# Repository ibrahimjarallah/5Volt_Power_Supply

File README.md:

# 5V Regulated Power Supply — L7805 Based PCB

> A classic linear regulated 5V power supply built around the L7805 voltage regulator.  
> Full-wave bridge rectifier input, multi-stage filtering, and power LED indicator.  
> Designed and laid out in **KiCad 9.0** — schematic + 2-layer PCB with full fabrication outputs.

---

## 📸 3D Views

| Front | Back |
|:---:|:---:|
|  |  |

## 🖼️ PCB Layout (2D)

| Front | Back |
|:---:|:---:|
|  |  |

## 🟤 PCB Layout — Copper Fill (2D)

| Front | Back |
|:---:|:---:|
|  |  |

## 📐 Schematic

---

## ⚡ Specifications

| Parameter             | Value                              |
|-----------------------|------------------------------------|
| Input Voltage (AC)    | 9V AC (transformer secondary)      |
| Rectified DC (unregulated) | ~12.7V DC                   |
| Output Voltage        | 5V DC regulated                    |
| Max Output Current    | 500mA continuous (no heatsink)     |
| Regulator             | L7805 (TO-220)                     |
| Rectifier             | Full-wave bridge — 4× 1N4007       |
| Bulk Capacitance      | 470µF                              |
| PCB Layers            | 2                                  |
| Designed With         | KiCad 9.0.7                        |

---

## 🔧 How It Works

### 1. Rectification
Four **1N4007** diodes arranged in a **full-wave bridge** configuration convert the 9V AC transformer secondary into pulsating DC (~12.7V peak).

### 2. Filtering
A three-stage capacitor filter smooths the rectified DC:
- **C1 (470µF)** — bulk electrolytic, handles low-frequency ripple
- **C2 (0.1µF)** — bypass capacitor, mid-frequency noise suppression
- **C3 (0.01µF)** — high-frequency decoupling at the regulator input

### 3. Regulation
The **L7805** linear regulator drops the unregulated ~12.7V down to a stable **5V DC output**, regardless of load variations up to 500mA.

### 4. Power Indicator
**D5 (LED)** with **R1 (1kΩ)** current-limiting resistor provides a visual power-on indication.  
LED current ≈ (5V − 2V) / 1kΩ ≈ **3mA**.

### 5. Connectors
Two **Phoenix Contact screw terminals (J1, J2)** — 3.5mm pitch — for robust AC input and DC output connections.

---

## 📦 Bill of Materials

| ID | Designator | Description | Quantity | Footprint |
|----|------------|-------------|----------|-----------|
| 1 | U1 | L7805 Voltage Regulator | 1 | TO-220-3 Vertical |
| 2 | D1–D4 | Diode 1N4007 (Bridge Rectifier) | 4 | DO-15 P2.54mm Vertical AnodeUp |
| 3 | D5 | LED 5mm | 1 | LED D5.0mm Horizontal |
| 4 | C1 | Capacitor 470µF electrolytic | 1 | Axial L10.0mm D6.0mm P15.00mm |
| 5 | C2 | Capacitor 0.1µF | 1 | Radial D4.0mm P1.50mm |
| 6 | C3 | Capacitor 0.01µF | 1 | Radial D4.0mm P1.50mm |
| 7 | R1 | Resistor 1kΩ | 1 | Axial DIN0204 L3.6mm P5.08mm |
| 8 | J1, J2 | Screw Terminal 2-pin 3.5mm | 2 | PhoenixContact MC 1.5/2-G-3.5 |

---

## 📁 Repository Structure

```
5Volt_Power_Supply/
├── 5Volt_Power_Supply.kicad_pro     # KiCad project file
├── 5Volt_Power_Supply.kicad_sch     # Schematic
├── 5Volt_Power_Supply.kicad_pcb     # PCB layout
├── BOM/
│   └── 5Volt_Power_Supply.csv       # Bill of materials
├── netlist/
│   └── 5Volt_Power_Supply.net       # Netlist
├── gerbers/                         # Fabrication Gerber files
│   ├── 5Volt_Power_Supply-F_Cu.gbr
│   ├── 5Volt_Power_Supply-B_Cu.gbr
│   ├── 5Volt_Power_Supply-F_Mask.gbr
│   ├── 5Volt_Power_Supply-B_Mask.gbr
│   ├── 5Volt_Power_Supply-F_Silkscreen.gbr
│   ├── 5Volt_Power_Supply-B_Silkscreen.gbr
│   ├── 5Volt_Power_Supply-F_Paste.gbr
│   ├── 5Volt_Power_Supply-B_Paste.gbr
│   ├── 5Volt_Power_Supply-Edge_Cuts.gbr
│   └── 5Volt_Power_Supply-job.gbrjob
├── drills/
│   ├── 5Volt_Power_Supply-PTH.drl   # Plated through-holes
│   └── 5Volt_Power_Supply-NPTH.drl  # Non-plated through-holes
├── 3D_VIEW/
│   ├── front_3d.png
│   └── back_3d.png
├── 2D_VIEW/
│   ├── 2d_view_front.png
│   ├── 2d_view_back.png
│   ├── 2d_view_front_filled.png
│   └── 2d_view_back_filled.png
└── Schematic_view/
    └── schematic_view.png
```

---

## 🖥️ Opening the Project

1. Install [KiCad 9.0+](https://www.kicad.org/download/)
2. Clone this repository:
   ```bash
   git clone https://github.com/ibrahimjarallah/5Volt_Power_Supply.git
   ```
3. Open `5Volt_Power_Supply.kicad_pro` in KiCad

---

## 🏭 Fabrication

All fabrication outputs are ready in the `gerbers/` and `drills/` folders.  
Compatible with standard PCB manufacturers (JLCPCB, PCBWay, OSHPark, etc.).

- Load `5Volt_Power_Supply-job.gbrjob` directly into any Gerber viewer or fab upload portal
- Drill files: `PTH` (plated) and `NPTH` (non-plated) provided separately

---

## ⚠️ Notes

- **No heatsink** — keep output current below 500mA to avoid thermal shutdown of L7805
- **Transformer not included** — requires external 9VAC center-tapped or standard secondary transformer
- **Polarized capacitors** — observe correct polarity for C1 during assembly

---

## 📄 License

This project is licensed under the **MIT License**.  
You are free to use, modify, and distribute it with attribution.

---

## 👤 Author

**Ibrahim Jarallah**  
GitHub: [ibrahimjarallah](https://github.com/ibrahimjarallah) \
LinkedIn: [ibrahimjarallah](https://www.linkedin.com/in/ibrahim-jarallah)

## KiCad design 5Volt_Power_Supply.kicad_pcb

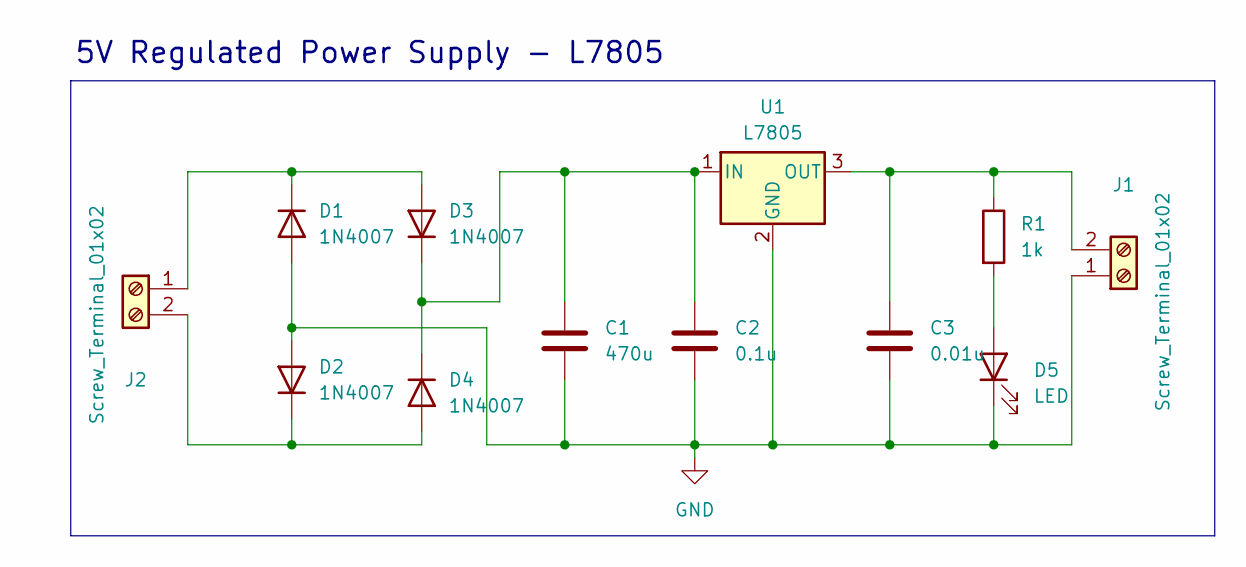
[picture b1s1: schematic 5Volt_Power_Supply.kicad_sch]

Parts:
C1: 470u; CP_Axial_L10.0mm_D6.0mm_P15.00mm_Horizontal
C2: 0.1u; CP_Radial_D4.0mm_P1.50mm
C3: 0.01u; CP_Radial_D4.0mm_P1.50mm
D1, D2, D3, D4: 1N4007; D_DO-15_P2.54mm_Vertical_AnodeUp
D5: LED; LED_D5.0mm_Horizontal_O1.27mm_Z3.0mm
J1, J2: Screw_Terminal_01x02; PhoenixContact_MC_1,5_2-G-3.5_1x02_P3.50mm_Horizontal
R1: 1k; R_Axial_DIN0204_L3.6mm_D1.6mm_P5.08mm_Horizontal
U1: L7805; TO-220-3_Vertical

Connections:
GND: C1.2, C2.2, C3.2, D1.2 (A), D2.2 (A), D5.1 (K), J1.1, U1.2 (GND)
unnamed: D1.1 (K), D3.2 (A), J2.1
unnamed: D2.1 (K), D4.2 (A), J2.2
unnamed: C1.1, C2.1, D3.1 (K), D4.1 (K), U1.1 (IN)
unnamed: D5.2 (A), R1.2
unnamed: C3.1, J1.2, R1.1, U1.3 (OUT)

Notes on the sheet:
5V Regulated Power Supply - L7805

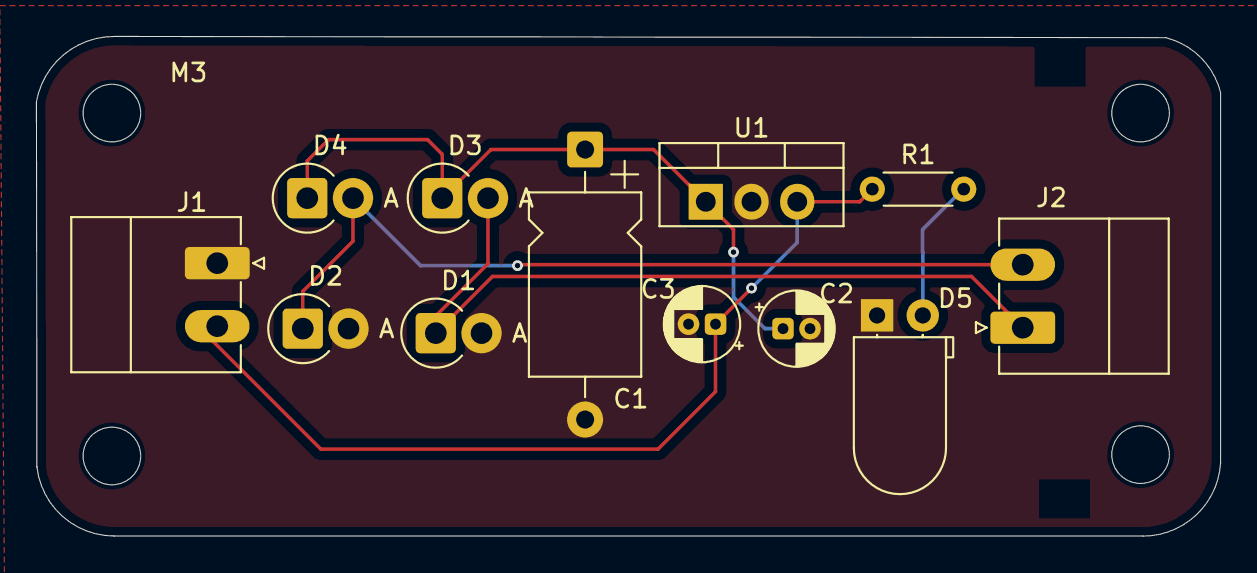
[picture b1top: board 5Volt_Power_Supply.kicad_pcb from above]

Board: 2 copper layers, 65.8 x 27.8 mm, 14 parts (0 on the bottom side), 6 nets.

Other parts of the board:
M3, M3#2: MountingHole_3.2mm_M3

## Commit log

2026-02-27 Initial commit: L7805 5V regulated power supply — schematic, PCB layout, Gerbers, BOM, netlist, 2D/3D views
2026-03-09 Update: added front/back 2D views, copper fill views, schematic view, design rules file, updated 3D views and PCB
2026-03-09 schematic pcb views
